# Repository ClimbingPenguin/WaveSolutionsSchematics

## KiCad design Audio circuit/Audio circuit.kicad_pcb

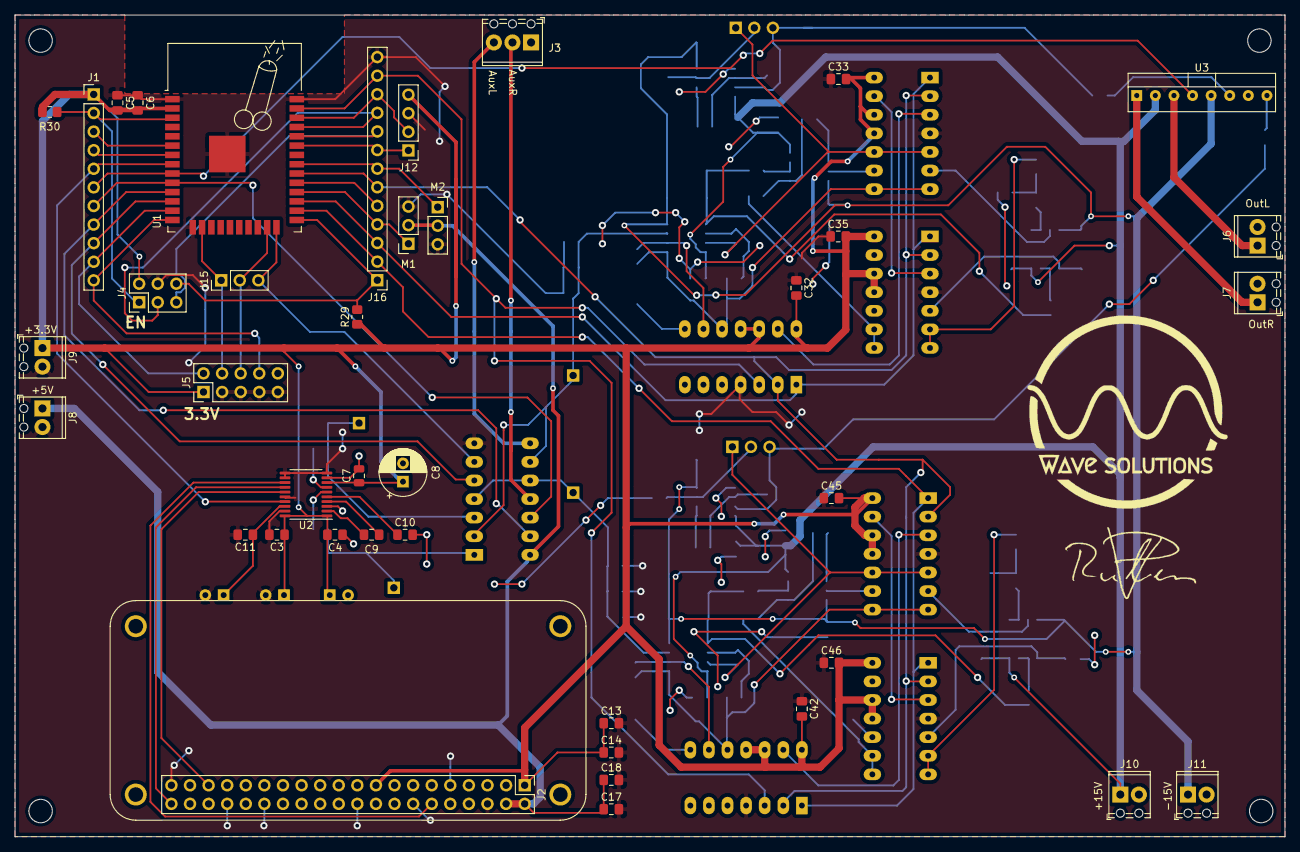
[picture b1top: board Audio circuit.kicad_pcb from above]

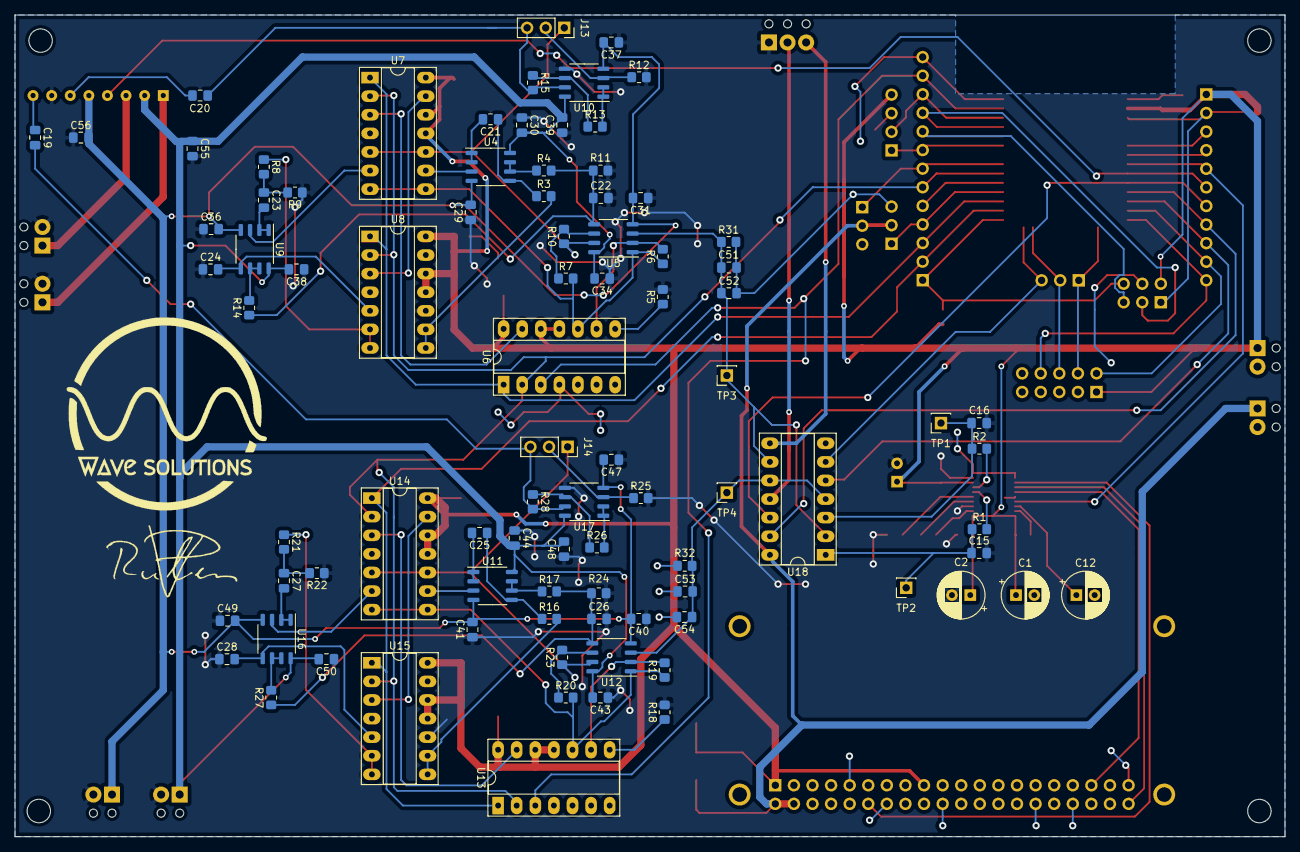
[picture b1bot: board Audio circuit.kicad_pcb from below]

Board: 2 copper layers, 173.5 x 112.2 mm, 128 parts (88 on the bottom side), 96 nets.

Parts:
C1, C2, C8, C12: 10u; CP_Radial_D6.3mm_P2.50mm
C3, C4, C11: 0.1u; C_0805_2012Metric_Pad1.18x1.45mm_HandSolder
C5, C6, C13, C14, C17, C18, C29, C30, C31, C32, C33, C34, C35, C36, C37, C38, C39, C40, C41, C42, C43, C44, C45, C46, C47, C48, C49, C50, C55, C56: 10u; C_0805_2012Metric_Pad1.18x1.45mm_HandSolder
C7: 0.1u; C_0805_2012Metric
C9, C10: 2.2u; C_0805_2012Metric_Pad1.18x1.45mm_HandSolder
C15, C16: 2.2n; C_0805_2012Metric_Pad1.18x1.45mm_HandSolder
C19, C20: 1u; C_0805_2012Metric_Pad1.18x1.45mm_HandSolder
C21, C25: 4.7n; C_0805_2012Metric_Pad1.18x1.45mm_HandSolder
C22, C26: 1n; C_0805_2012Metric_Pad1.18x1.45mm_HandSolder
C23, C27: 100u; C_0805_2012Metric_Pad1.18x1.45mm_HandSolder
C24, C28: 100n; C_0805_2012Metric_Pad1.18x1.45mm_HandSolder
C51, C52, C53, C54: 10p; C_0805_2012Metric_Pad1.18x1.45mm_HandSolder
J1: Conn_01x11_Female; PinHeader_1x11_P2.54mm_Vertical
J2: Conn_02x20_Odd_Even; RaspberryPiZero2W
J3: Screw_Terminal_01x03; TerminalBlock_Phoenix_MPT-0,5-3-2.54_1x03_P2.54mm_Horizontal
J4: Conn_02x03_Odd_Even; PinHeader_2x03_P2.54mm_Vertical
J5: Conn_02x05_Odd_Even; PinHeader_2x05_P2.54mm_Vertical
J6, J7, J8, J9, J10, J11: Screw_Terminal_01x02; TerminalBlock_Phoenix_MPT-0,5-2-2.54_1x02_P2.54mm_Horizontal
J12: Conn_01x04_Female; PinHeader_1x04_P2.54mm_Vertical
J13, J14: Screw_Terminal_01x03; PinSocket_1x03_P2.54mm_Vertical
J15: Conn_01x03_Female; PinHeader_1x03_P2.54mm_Vertical
J16: Conn_01x13_Female; PinHeader_1x13_P2.54mm_Vertical
M1, M2: Motor_Servo; PinSocket_1x03_P2.54mm_Vertical
R1, R2: 470; R_0805_2012Metric_Pad1.20x1.40mm_HandSolder
R3, R16: 3.5k; R_0805_2012Metric_Pad1.20x1.40mm_HandSolder
R4, R9, R14, R17, R22, R27: 1k; R_0805_2012Metric_Pad1.20x1.40mm_HandSolder
R5, R18: 5k; R_0805_2012Metric_Pad1.20x1.40mm_HandSolder
R6, R7, R10, R15, R19, R20, R23, R28, R29, R30: 10k; R_0805_2012Metric_Pad1.20x1.40mm_HandSolder
R8, R21: 3.9k; R_0805_2012Metric_Pad1.20x1.40mm_HandSolder
R11, R24: 1.2k; R_0805_2012Metric_Pad1.20x1.40mm_HandSolder
R12, R25: 100k; R_0805_2012Metric_Pad1.20x1.40mm_HandSolder
R13, R26: 2k; R_0805_2012Metric_Pad1.20x1.40mm_HandSolder
R31, R32: 4.7k; R_0805_2012Metric_Pad1.20x1.40mm_HandSolder
TP1, TP2, TP3, TP4: TestPoint; PinSocket_1x01_P2.54mm_Vertical
U1: ESP32-WROOM-32D; ESP32-WROOM-32
U2: PCM5100; TSSOP-20_4.4x6.5mm_P0.65mm
U3: TDA7264; TO-220-8_Vertical
U4, U5, U9, U10, U11, U12, U16, U17: BA4558F-E2; SOP-8_3.9x4.9mm_P1.27mm
U6, U7, U8, U13, U14, U15: MCP42010-I.P; DIP-14_W7.62mm_Socket_LongPads
U18: CD4016BE; DIP-14_W7.62mm_Socket_LongPads

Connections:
+3V3: C1.1, C2.1, C3.1, C4.1, C5.1, C6.1, C7.1, C8.1, C13.1, C14.1, C32.2, C33.2, C35.2, C42.2, C45.2, C46.2, J1.1, J2.1, J2.17, J4.2, J5.1, J9.1, J12.4, R29.1, R30.1, U1.2, U2.1, U2.8, U2.20, U6.11, U6.12, U6.14, U7.11, U7.12, U7.14, U8.11, U8.12, U8.14, U13.11, U13.12, U13.14, U14.11, U14.12, U14.14, U15.11, U15.12, U15.14
+5V: C17.1, C18.1, J2.2, J2.4, J8.1, M1.2, M2.2, U18.14
+15V: C30.2, C34.2, C38.2, C39.2, C43.2, C44.2, C48.2, C50.2, C55.1, J10.1, U3.2, U4.8, U5.8, U9.8, U10.8, U11.8, U12.8, U16.8, U17.8
-15V: C29.2, C31.2, C36.2, C37.2, C40.2, C41.2, C47.2, C49.2, C56.2, J11.1, U3.5, U4.4, U5.4, U9.4, U10.4, U11.4, U12.4, U16.4, U17.4
/Analog/L_aux_in: J3.3, U18.8
/Analog/L_out: J6.1, U3.3
/Analog/L_pi_in: C15.1, R1.1, TP2.1, U18.1
/Analog/Left/L_in: C51.2, C52.1, R31.1, TP3.1, U5.3, U18.2, U18.9
/Analog/Left/L_out: C20.2, J13.3, R15.2, U10.7
/Analog/Left/Pot1.1: U6.13, U7.3
/Analog/Left/Pot1.2: U7.13, U8.3
/Analog/Left/balans_fb: C22.1, R4.2, R11.2, R14.1, U5.5
/Analog/Left/balans_in: R6.1, R7.2, U5.1, U6.10, U7.7, U7.8
/Analog/Left/balans_uit: J13.1, R10.1, U5.7, U7.5, U7.10
/Analog/R_aux_in: J3.2, U18.11
/Analog/R_out: J7.1, U3.1
/Analog/R_pi_in: C16.2, R2.1, TP1.1, U18.3
/Analog/Right/Pot2.1: U13.13, U14.3
/Analog/Right/Pot2.2: U14.13, U15.3
/Analog/Right/R_in: C53.2, C54.1, R32.1, TP4.1, U12.3, U18.4, U18.10
/Analog/Right/R_out: C19.2, J14.3, R28.2, U17.7
/Analog/Right/balans_fb: C26.1, R17.2, R24.2, R27.1, U12.5
/Analog/Right/balans_in: R19.1, R20.2, U12.1, U13.10, U14.7, U14.8
/Analog/Right/balans_uit: J14.1, R23.1, U12.7, U14.5, U14.10
/CSL: J16.3, U1.27, U6.1, U7.1, U8.1
/CSR: J16.2, U1.26, U13.1, U14.1, U15.1
/ESP_EN: J1.2, J4.1, R30.2, U1.3
/ESP_IO0: J4.6, J16.1, R29.2, U1.25
/ESP_RXD: J4.5, J16.9, U1.34
/ESP_TCK: J5.4, J15.1, U1.16
/ESP_TDI: J1.11, J5.8, U1.14
/ESP_TDO: J5.6, J15.2, U1.23
/ESP_TMS: J1.10, J5.2, U1.13
/ESP_TXD: J4.3, J16.10, U1.35
/IO5: J16.5, U1.29
/IO34: J1.3, U1.6
/IO35: J1.4, U1.7
/MOSI: J16.12, U1.37, U6.3, U13.3
/MUTE_eind: J1.6, U1.9, U3.4
/PCM_BCK: J2.12, U2.13
/PCM_DIN: J2.40, U2.14
/PCM_LRCK: J2.35, U2.15
/PCM_MUTE: J1.5, U1.8, U2.17
/SCK: J16.6, U1.30, U6.2, U7.2, U8.2, U13.2, U14.2, U15.2
/SCL: J12.2, J16.11, U1.36
/SDA: J12.1, J16.8, U1.33
/SW_AUXL: J15.3, U1.24, U18.6
/SW_AUXR: J1.7, U1.10, U18.12
/SW_PIL: J1.8, U1.11, U18.13
/SW_PIR: J1.9, U1.12, U18.5
/ServoL: J16.4, M1.1, U1.28
/ServoR: J16.7, M2.1, U1.31
Earth: C1.2, C3.2, C5.2, C6.2, C11.2, C12.2, C13.2, C14.2, C17.2, C18.2, C32.1, C33.1, C35.1, C42.1, C45.1, C46.1, C51.1, C52.2, C53.1, C54.2, J2.6, J2.9, J2.14, J2.20, J2.30, J2.34, J2.39, J4.4, J5.3, J5.5, J5.7, J5.9, J8.2, J9.2, J12.3, J16.13, M1.3, M2.3, R31.2, R32.2, U1.1, U1.15, U1.38, U1.39, U2.10, U2.11, U2.12, U2.16, U2.19, U6.4, U7.4, U8.4, U13.4, U14.4, U15.4, U18.7
GNDA: C2.2, C4.2, C7.2, C8.2, C10.2, C15.2, C16.1, C22.2, C24.1, C26.2, C28.1, C29.1, C30.1, C31.1, C34.1, C36.1, C37.1, C38.1, C39.1, C40.1, C41.1, C43.1, C44.1, C47.1, C48.1, C49.1, C50.1, C55.2, C56.1, J3.1, J6.2, J7.2, J10.2, J11.2, R5.2, R9.1, R11.1, R12.2, R18.2, R22.1, R24.1, R25.2, U2.3, U2.9, U3.7, U8.10, U10.5, U15.10, U17.5
unnamed: C9.1, U2.2
unnamed: C9.2, U2.4
unnamed: C10.1, U2.5
unnamed: C11.1, C12.1, U2.18
unnamed: C19.1, U3.8
unnamed: C20.1, U3.6
unnamed: C21.1, R3.1, U4.5
unnamed: C21.2, U4.1, U4.2
unnamed: C23.1, R8.2, R9.2
unnamed: C23.2, U9.1, U9.2
unnamed: C24.2, U8.5, U9.5
unnamed: C25.1, R16.1, U11.5
unnamed: C25.2, U11.1, U11.2
unnamed: C27.1, R21.2, R22.2
unnamed: C27.2, U16.1, U16.2
unnamed: C28.2, U15.5, U16.5
unnamed: J13.2, R12.1, U10.3
unnamed: J14.2, R25.1, U17.3
unnamed: R1.2, U2.6
unnamed: R2.2, U2.7
unnamed: R3.2, U8.8, U8.9
unnamed: R4.1, U4.6, U4.7
unnamed: R5.1, U6.8
unnamed: R6.2, U5.2, U6.9
unnamed: R8.1, U8.6, U8.7
unnamed: R7.1, R10.2, U5.6
unnamed: R13.1, R15.1, U10.6
unnamed: R13.2, U10.1, U10.2
unnamed: R14.2, U9.6, U9.7
unnamed: R16.2, U15.8, U15.9
unnamed: R17.1, U11.6, U11.7
unnamed: R18.1, U13.8
unnamed: R19.2, U12.2, U13.9
unnamed: R20.1, R23.2, U12.6
unnamed: R21.1, U15.6, U15.7
unnamed: R26.1, R28.1, U17.6
unnamed: R26.2, U17.1, U17.2
unnamed: R27.2, U16.6, U16.7
unnamed: U4.3, U7.9
unnamed: U7.6, U9.3
unnamed: U11.3, U14.9
unnamed: U14.6, U16.3
